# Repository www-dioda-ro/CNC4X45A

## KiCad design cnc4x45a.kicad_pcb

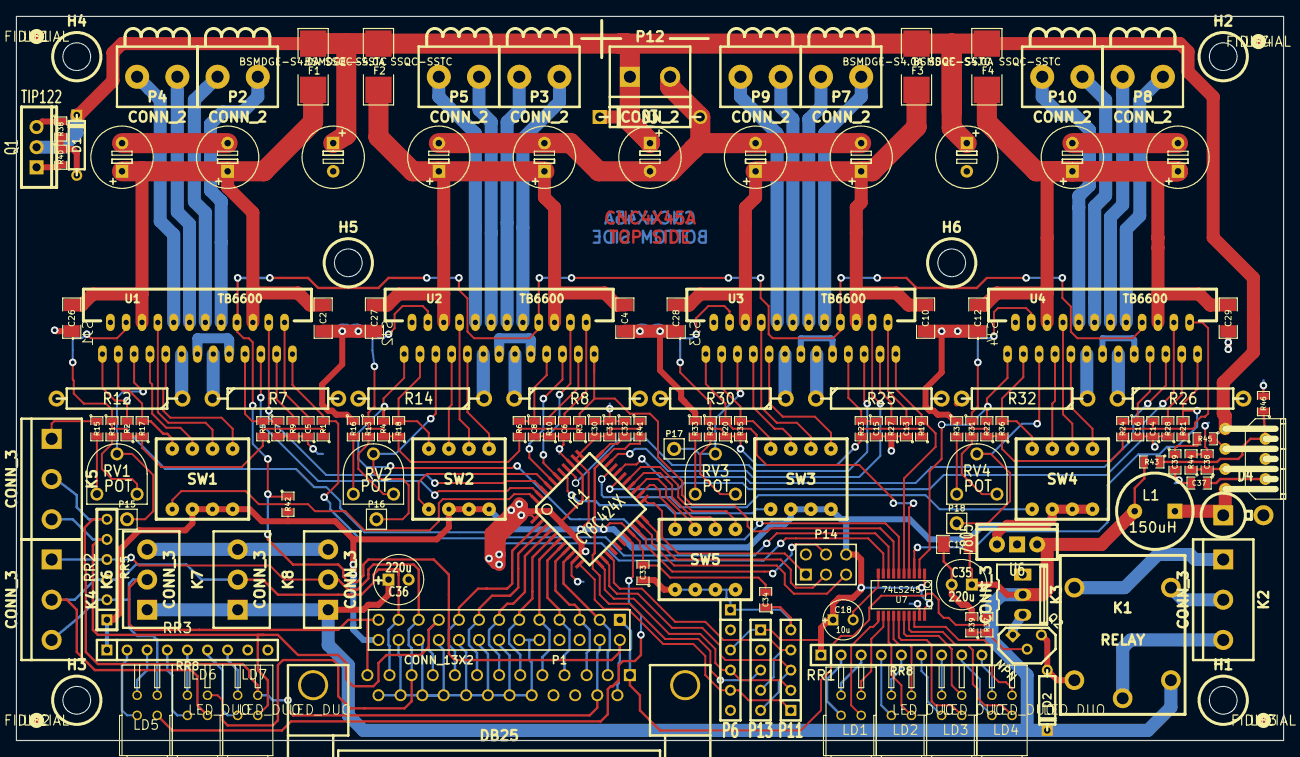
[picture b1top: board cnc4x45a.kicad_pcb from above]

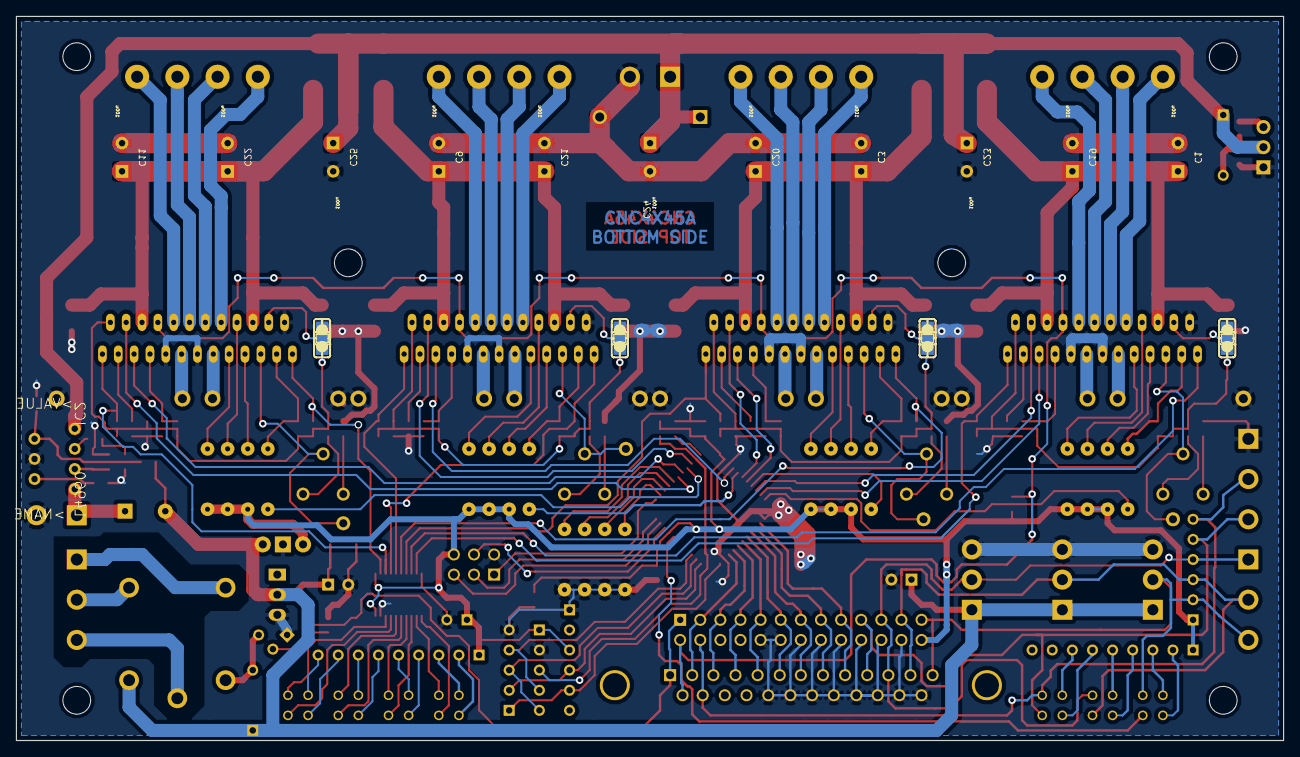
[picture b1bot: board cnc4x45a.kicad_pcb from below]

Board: 2 copper layers, 160.0 x 91.4 mm, 164 parts (4 on the bottom side), 157 nets.

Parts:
C1, C3, C9, C11, C19, C20, C21, C22, C23, C24, C25: 100u; CELEC_3.5MM_8MM
C2, C4, C10, C12, C17, C26, C27, C28, C29: 1u; SM1206
C5, C6, C13, C14: C; SM0805
C7, C8, C15, C16: 100n; SM0805
C18: 10u; C1V5
C30, C34: .1u; SM0805
C31, C32, C33: 1u; SM0805
C35, C36: 220u; C1V7
C37: 2.2uF; SM0805
C38: 2.2nF; SM0805
C39: 33nf; SM0805
D1: 39V; D3
D2: DIODE; D3
D3: Transil 1.5KE39; D5
D4: byw80 / STTH3R02; DO-201AD_Vertical_RM15
F1, F2, F3, F4: BSMDGE-S4.0A SSQC-SSTC; SSQC
H1, H2, H3, H4, H5, H6: MOUNT_HOLE; MountingHole_3-5mm_RevA_Date21Jun2010
IC1: CY8C424X; TQFP44
IC2: L4960; L4960-HEPTAWATT
J1: DB25; DB25FC
K1: RELAY; LEG-XX
K2, K4, K5: CONN_3; bornier3
K3: CONN_3; kk100_22-23-2031
K6, K7, K8: CONN_3; bornier3_3.81
L1: 150uH; INDUCTOR_V
LB1, LB2, LB3, LB4: FIDUCIAL; olimex-SPARKFUNEAGLE-6-6-07_FIDUCIAL-1.5X3
LD1, LD2, LD3, LD4, LD5, LD6, LD7: LED_DUO
P1: CONN_13X2; pin_array_13x2
P2, P3, P4, P5, P7, P8, P9, P10: CONN_2; bornier2_Lsign
P6: CONN_6; SIL-6
P11, P13: CONN_5; SIL-5
P12: CONN_2; bornier2
P14: CONN_6; pin_array_3x2
P15, P16, P17, P18: CONN_1; PIN_ARRAY_1
Q1: TIP122; TO220_VERT
Q2: NPN; TO92
R1, R2, R3, R4, R9, R10, R19, R20, R21, R22, R27, R28: 51k; SM0805
R5, R6, R23, R24: R; SM0805
R7, R8, R12, R14, R25, R26, R30, R32: .20; R6_018
R11, R13, R29, R31: 75k; SM0805
R15, R16, R33, R34: 8k06; SM0805
R17, R18, R35, R36: 10k; SM0805
R37, R40, R46: 4k7; SM0805
R38: 220; SM0805
R39: 100k; SM0805
R41: 24k; SM0805
R42: 20k; SM0805
R43: 6k2; SM0805
R44: 4k3; SM0805
R45: 15k; SM0805
RR1, RR3: RR8; r_pack8
RR2: RR5; r_pack5
RV1, RV2, RV3, RV4: POT; TRIM_POT
SJ1, SJ2, SJ3, SJ4: JUMPER_SJ2W; olimex-JUMPER_SJ_2
SW1, SW2, SW3, SW4, SW5: DIPS_04; DIPS-DS04
U1, U2, U3, U4: TB6600; HZIP25-P-1.00F
U6: 7805; 78XX_VERT
U7: 74LS245; SSOP20

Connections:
+5V: C18.1, C30.2, C31.2, C33.2, C34.2, IC1.19, IC1.34, IC1.35, P1.26, P6.3, P13.1, P14.6, R41.1, R42.2, RR1.1, RR2.1, RR3.1, SW1.6, SW1.7, SW1.8, SW2.6, SW2.7, SW2.8, SW3.6, SW3.7, SW3.8, SW4.6, SW4.7, SW4.8, U6.VO, U7.1, U7.20
+12V: C17.1, C35.1, C36.1, D2.2, K1.B2, K3.2, K6.1, K7.1, K8.1, L1.2, R43.2, U6.VI
//XRES: IC1.32, P13.3, R41.2
/A-Alert: R22.2, U4.1, U7.2
/A-DIR: IC1.28, U4.22
/A-LTQ: IC1.30, SW4.5
/A-MOut: R21.2, U4.25, U7.3
/A-STEP: IC1.29, U4.21
/AVcc: C11.1, C12.1, C22.1, C29.2, F4.1, U4.6, U4.20
/SWD CLK: IC1.14, P11.4, P13.4
/SWD IO: IC1.13, P11.3, P13.5
/V_Alim: C23.1, C24.1, C25.1, D1.2, D3.2, F1.2, F2.2, F3.2, F4.2, IC2.1, P12.1, Q1.3
/X-Alert: R2.2, U1.1, U7.8
/X-DIR: IC1.42, U1.22
/X-LTQ: IC1.44, SW1.5
/X-MOut: R1.2, U1.25, U7.9
/X-STEP: IC1.43, U1.21
/XVcc: C1.1, C2.1, C19.1, C26.2, F1.1, U1.6, U1.20
/Y-Alert: R4.2, U2.1, U7.6
/Y-DIR: IC1.39, U2.22
/Y-LTQ: IC1.41, SW2.5
/Y-MOut: R3.2, U2.25, U7.7
/Y-STEP: IC1.40, U2.21
/YVcc: C3.1, C4.1, C20.1, C27.2, F2.1, U2.6, U2.20
/Z-Alert: R20.2, U3.1, U7.4
/Z-DIR: IC1.31, U3.22
/Z-LTQ: IC1.38, SW3.5
/Z-MOut: R19.2, U3.25, U7.5
/Z-STEP: IC1.37, U3.21
/ZVcc: C9.1, C10.1, C21.1, C28.2, F3.1, U3.6, U3.20
/a_min: J1.10, K5.3, LD7.LV_K, P1.19, RR2.5
/blink: IC1.18, LD5.LV_K
/clk: IC1.22, P14.3
/clka: IC1.2, J1.9, P1.17
/clkx: IC1.8, J1.3, P1.5
/clky: IC1.6, J1.5, P1.9
/clkz: IC1.4, J1.7, P1.13
/dira: IC1.3, J1.8, P1.15
/dirx: IC1.9, J1.2, P1.3
/diry: IC1.7, J1.4, P1.7
/dirz: IC1.5, J1.6, P1.11
/e_stop: J1.15, K5.2, LD7.LR_K, P1.4, RR2.6
/ena: J1.14, P1.2, R42.1, U1.18, U2.18, U3.18, U4.18
/miso: IC1.21, P14.5
/mosi: IC1.20, P14.4
/spindle: J1.1, P1.1, R37.1
/ssel0: IC1.23, P14.1
/x_min: J1.13, K4.3, K6.2, LD5.LR_K, P1.25, RR2.2
/y_min: J1.12, K4.2, K7.2, LD6.LV_K, P1.23, RR2.3
/z_min: J1.11, K4.1, K8.2, LD6.LR_K, P1.21, RR2.4
GND: C1.2, C2.2, C3.2, C4.2, C5.1, C6.1, C7.2, C8.2, C9.2, C10.2, C11.2, C12.2, C13.1, C14.1, C15.2, C16.2, C17.2, C18.2, C19.2, C20.2, C21.2, C22.2, C23.2, C24.2, C25.2, C26.1, C27.1, C28.1, C29.1, C30.1, C31.1, C32.1, C33.1, C34.1, C35.2, C36.2, C37.2, C38.2, C39.2, D3.1, D4.1, IC1.1, IC1.10, IC1.36, IC2.4, J1.18, J1.19, J1.20, J1.21, J1.22, J1.23, J1.24, J1.25, K3.3, K5.1, K6.3, K7.3, K8.3, P1.10, P1.12, P1.14, P1.16, P1.18, P1.20, P1.22, P1.24, P6.1, P11.5, P12.2, P13.2, P14.2, Q1.1, Q2.1, R7.2, R8.2, R9.1, R10.1, R12.2, R14.2, R15.1, R16.1, R25.2, R26.2, R27.1, R28.1, R30.2, R32.2, R33.1, R34.1, R39.2, R40.2, R44.2, R46.2, SJ1.3, SJ2.3, SJ3.3, SJ4.3, SW5.5, SW5.6, SW5.7, SW5.8, U1.2, U1.13, U1.17, U2.2, U2.13, U2.17, U3.2, U3.13, U3.17, U4.2, U4.13, U4.17, U6.GND, U7.10, U7.19
unnamed: Q1.2, R38.1
unnamed: D1.1, R38.2, R40.1
unnamed: Q2.2, R37.2, R39.1
unnamed: D2.1, K1.B1, Q2.3
unnamed: LD1.LR_A, RR1.3
unnamed: LD1.LV_A, RR1.2
unnamed: LD4.LR_A, RR1.9
unnamed: LD4.LV_A, RR1.8
unnamed: LD3.LR_A, RR1.7
unnamed: LD3.LV_K, U7.15
unnamed: LD3.LV_A, RR1.6
unnamed: LD2.LR_A, RR1.5
unnamed: LD2.LV_K, U7.13
unnamed: LD2.LV_A, RR1.4
unnamed: IC1.24, SW5.4
unnamed: K1.NA, K2.2
unnamed: K1.C, K2.3
unnamed: K1.NF, K2.1
unnamed: IC1.25, SW5.3
unnamed: SW4.3, U4.7
unnamed: SW4.2, U4.8
unnamed: SW4.1, U4.9
unnamed: P10.1, U4.10
unnamed: P10.2, U4.12
unnamed: P8.1, U4.14
unnamed: P8.2, U4.16
unnamed: R32.1, U4.11
unnamed: R26.1, U4.15
unnamed: P18.1, RV4.2, U4.5
unnamed: R28.2, U4.23
unnamed: R31.2, RV4.3
unnamed: R34.2, RV4.1
unnamed: R36.2, SW4.4, U4.3
unnamed: IC1.11, P6.5, P11.1
unnamed: LD4.LR_K, U7.18
unnamed: LD4.LV_K, U7.17
unnamed: LD3.LR_K, U7.16
unnamed: LD2.LR_K, U7.14
unnamed: LD1.LR_K, U7.12
unnamed: IC1.27, SW5.1
unnamed: IC1.26, SW5.2
unnamed: C16.1, R24.2, U4.19
unnamed: C14.2, R21.1, R22.1, R24.1, R31.1, R36.1, SJ4.1, SJ4.2, U4.4, U4.24
unnamed: R33.2, RV3.1
unnamed: R16.2, RV2.1
unnamed: R15.2, RV1.1
unnamed: IC2.3, R45.1
unnamed: C32.2, IC1.33
unnamed: IC2.2, R43.1, R46.1
unnamed: C38.1, IC2.5, R44.1
unnamed: C37.1, IC2.6
unnamed: D4.2, IC2.7, L1.1
unnamed: C39.1, R45.2
unnamed: LD6.LV_A, RR3.4
unnamed: LD7.LV_A, RR3.6
unnamed: LD6.LR_A, RR3.5
unnamed: LD7.LR_A, RR3.7
unnamed: LD5.LR_A, RR3.3
unnamed: LD5.LV_A, RR3.2
unnamed: LD1.LV_K, U7.11
unnamed: R17.2, SW1.4, U1.3
unnamed: P2.2, U1.16
unnamed: R11.2, RV1.3
unnamed: SW1.3, U1.7
unnamed: R7.1, U1.15
unnamed: P2.1, U1.14
unnamed: R9.2, U1.23
unnamed: P4.2, U1.12
unnamed: R12.1, U1.11
unnamed: P4.1, U1.10
unnamed: SW1.1, U1.9
unnamed: SW1.2, U1.8
unnamed: P15.1, RV1.2, U1.5
unnamed: IC1.12, P6.4, P11.2
unnamed: C5.2, R1.1, R2.1, R5.1, R11.1, R17.1, SJ1.1, SJ1.2, U1.4, U1.24
unnamed: C7.1, R5.2, U1.19
unnamed: R27.2, U3.23
unnamed: SW3.1, U3.9
unnamed: SW3.3, U3.7
unnamed: SW3.2, U3.8
unnamed: P9.1, U3.10
unnamed: P9.2, U3.12
unnamed: P7.1, U3.14
unnamed: P7.2, U3.16
unnamed: R30.1, U3.11
unnamed: R25.1, U3.15
unnamed: R29.2, RV3.3
unnamed: P17.1, RV3.2, U3.5
unnamed: R35.2, SW3.4, U3.3
unnamed: C13.2, R19.1, R20.1, R23.1, R29.1, R35.1, SJ3.1, SJ3.2, U3.4, U3.24
unnamed: C15.1, R23.2, U3.19
unnamed: R13.2, RV2.3
unnamed: C6.2, R3.1, R4.1, R6.1, R13.1, R18.1, SJ2.1, SJ2.2, U2.4, U2.24
unnamed: R18.2, SW2.4, U2.3
unnamed: R10.2, U2.23
unnamed: SW2.3, U2.7
unnamed: P16.1, RV2.2, U2.5
unnamed: SW2.2, U2.8
unnamed: SW2.1, U2.9
unnamed: R14.1, U2.11
unnamed: R8.1, U2.15
unnamed: P5.2, U2.12
unnamed: P5.1, U2.10
unnamed: P3.1, U2.14
unnamed: P3.2, U2.16
unnamed: C8.1, R6.2, U2.19
